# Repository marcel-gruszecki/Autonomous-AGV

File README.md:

# Autonomous AGV Fleet — ESP32 Line Followers in a Scale Warehouse

A fleet of two autonomous guided vehicles (AGVs) that serve a self-built scale
warehouse. Each vehicle runs on a custom ESP32 PCB and follows a taped line network.
A Python control server plans collision-free routes for both robots, and a warehouse
layer on top of it turns deliveries and customer orders into transport jobs.

The project covers the full development cycle: electrical schematic and PCB, hardware
assembly, embedded firmware, multi-robot path planning, and warehouse logistics.

The mechanical platform comes from the *OSOYOO 2WD Robot Car Starter Kit for Arduino*,
which was used as a chassis and drivetrain base only. The stock Arduino Uno and its
motor shield were removed and replaced with a self-designed ESP32-WROOM carrier board,
adding Wi-Fi connectivity and a 32-bit MCU in place of the original 8-bit controller.

## Demo
https://github.com/user-attachments/assets/aa6393ad-4d51-4d18-ae9f-6a0b75ac840b

## Hardware

**Custom PCB (KiCad, manufactured by PCBWay)** — a single-board carrier designed from
scratch, integrating:

- Power section based on LM2596 step-down converters (7.4 V Li-ion pack → 5 V / 3.3 V rails)
- Separate power distribution path for the motor driver
- Connectors for a three-channel TCRT5000 optical line-sensor array
- ESP32-WROOM main circuit with an optimised keepout zone under the RF antenna

**Drivetrain and sensing** — 2× DC gear motors driven through a Model-X dual H-bridge
(PWM speed control on ENA/ENB), 3× TCRT5000 reflective sensors for line detection.

*Electrical schematic: battery and power conversion, ESP32-WROOM module, motor
driver interface, and the line-sensor array (KiCad).*

The board was assembled by hand (T12 soldering station), including component selection,
mechanical integration, and debugging of short-circuit and polarity faults on the first
revision. Both robots use the same PCB revision.

## Warehouse layout

*Scale 1:1, board 200 × 100 cm. CAD source: `Warehouse_model/`.*

The track is a graph of 16 nodes, laid out with 3 cm wide tape. Coordinates are in cm,
(0, 0) is the top-left corner, x grows to the right and y downwards.

| Node | Role | Position |
|------|------|----------|
| `IN1`, `IN2` | Inbound stations — goods arrive here (green) | left edge, y = 38 / 62 |
| `OUT1`, `OUT2` | Outbound stations — goods leave here (red) | right edge, y = 38 / 62 |
| `C1`, `C2`, `C3` | Chargers / robot home positions (blue) | top edge, x = 60 / 100 / 140 |
| `R1`, `R2`, `R3` | Racks, one item type each: `A`→`R1`, `B`→`R2`, `C`→`R3` (yellow) | bottom edge, x = 60 / 100 / 140 |
| `T60` … `T140`, `B60` … `B140` | Intersections of the two horizontal lines with the three vertical lines | y = 38 / 62 |

Stations, chargers and racks are *fields* — dead ends of a line with a stop bar.
A robot drives onto a field, stops on the bar, and turns 180° to leave. The two ends
of each short vertical connector (e.g. `T60`–`B60`) are treated as one place, so only
one robot can be on them at a time.

## Software architecture

```
 warehouse.py  ──HTTP /goal, /status──▶  serwer.py  ◀──HTTP /command, /done──  ESP32 robot 1
 (stock, orders,                         (CBS path planning,                    ESP32 robot 2
  task dispatch)                          command scheduling)
```

- `OSOYOO/` — ESP32 firmware, C++ on the Arduino framework (PlatformIO). PD line
  following on three sensors, turns at intersections, 180° turns on fields.
- `Server/serwer.py` — control server (Flask). Plans paths for all robots together
  and hands each robot one command at a time.
- `Server/mapf.py` — multi-agent path finding: Conflict-Based Search
  with space-time A*, turned into an Action Dependency Graph
  so the robots stay collision-free even though they do not
  move in lock-step.
- `Server/warehouse.py` — warehouse layer: keeps the rack stock, queues deliveries
  and orders, and decides which robot goes where.
- `Scheme/` — KiCad schematic, PCB layout, and Gerber files.
- `Warehouse_model/` — CAD drawing of the warehouse board.

### Robot ↔ server protocol

The robot polls `GET /command?robot=<id>` every 100 ms and receives plain text
`"<id> <COMMAND>"` (`"0 STOP"` = nothing to do). After executing it, the robot confirms
with `GET /done?robot=<id>&id=<id>`. Until the confirmation arrives, the server keeps
returning the same command; the robot recognises the id it has already executed, so a
lost confirmation never makes it drive twice.

| Command | Meaning |
|---------|---------|
| `FORWARD [n]` | Follow the line and stop on the stop bar of a field |
| `FORWARD_AFTER_LINE [n]` | Follow the line and stop with the axle on an intersection; `n` = number of intersections to pass (straight drives are merged) |
| `TURN_LEFT`, `TURN_RIGHT` | Rotate 90° on an intersection |
| `RETURN_LEFT`, `RETURN_RIGHT` | Rotate 180° on a field, away from the neighbouring field |
| `STOP` | Stand still |

### Server HTTP API

| Endpoint | Used by | Description |
|----------|---------|-------------|
| `GET /command?robot=<id>` | robot | Current command, see above |
| `GET /done?robot=<id>&id=<cmd id>` | robot | Confirms a command, updates the robot position |
| `GET /goal?robot=<id>&to=<node>` | warehouse | Sets a goal node and replans all robots; `400 {"error": ...}` if the node is taken |
| `GET /status` | warehouse | State of all robots, see [JSON formats](#json-formats) |

## Getting started

### Requirements

- PlatformIO (CLI or the VS Code extension)
- Python 3.8+ with `pip install -r Server/requirements.txt` (Flask)
- The PC running the server and both robots on the same Wi-Fi network

### 1. Configure and flash each robot

```bash
cd OSOYOO/include
cp config.example.hpp config.hpp
```

Edit `config.hpp`:

```cpp
const char* const WIFI_SSID  = "your-wifi";
const char* const WIFI_PASS  = "your-password";
const char* const SERVER_URL = "http://192.168.1.10:8080";   // IP of the PC running serwer.py

#define ROBOT_ID "1"   // "1" for the first robot, "3" for the second one
```

The robot ids must match the server: robot `1` starts on charger `C1`, robot `3` on
`C3` (configured in `robots` in `Server/serwer.py`). `config.hpp` holds your Wi-Fi
password and is ignored by git.

Flash the robot (repeat for the second one with a different `ROBOT_ID`):

```bash
cd OSOYOO
pio run -t upload          # upload_port in platformio.ini: /dev/ttyUSB0
pio device monitor         # optional: serial log, 115200 baud
```

### 2. Place the robots

Put robot `1` on `C1` and robot `3` on `C3`, facing the edge of the board (away from
the track). On the first start the server assumes exactly this position. After that
it remembers the positions in `server_state.json`; delete that file whenever you put
the robots back on their chargers by hand.

### 3. Start the warehouse and the server

In two terminals, inside `Server/`:

```bash
python warehouse.py            # warehouse layer, interactive terminal
python serwer.py               # control server on port 8080
```

`warehouse.py` keeps retrying until the server answers, so the start order does not
matter. Once the robots connect to Wi-Fi they start polling for commands.

`warehouse.py` options:

```bash
python warehouse.py --simulate [--seed 42]                       # random deliveries and orders
python warehouse.py --replay logs/session_YYYYMMDD_HHMMSS.json   # repeat a recorded session
python warehouse.py --replay <file> --speed 2                    # ... twice as fast
```

`serwer.py --random` sends the robots to random free fields without the warehouse
(useful for testing the path planning alone).

### 4. Give the warehouse work

```
>>> in A IN2       # item A arrived at IN2 -> a robot stores it on rack R1
>>> out A OUT1     # item A requested at OUT1 -> a robot takes it from R1 to OUT1
>>> status         # racks, waiting goods, waiting orders, robot tasks
>>> quit
```

Task priority: orders first (from the rack if it has stock, otherwise cross-docking
straight from an inbound station if the item is waiting there), then storing waiting
goods on racks that are not full (capacity 5). A robot with nothing to do returns to
its charger.

## JSON formats

All files are written atomically (to a `.tmp` file, then renamed), so a crash never
leaves a half-written file. Thanks to them both programs can be restarted at any time
and continue where they stopped.

### `Server/server_state.json` — written by `serwer.py`

Saved after every change of a robot's state.

```json
{
  "next_id": 1761400000,
  "robots": {
    "1": {
      "position": "C1",
      "heading": "S",
      "goal": "R1",
      "actions": [
        {"cmd": "FORWARD", "to": "R1", "heading": "S", "seq": 4, "deps": [["3", 2]]}
      ],
      "current": {
        "id": 1761399999,
        "cmd": "FORWARD_AFTER_LINE 2",
        "actions": [
          {"cmd": "FORWARD", "to": "T60", "heading": "S", "seq": 2, "deps": []},
          {"cmd": "FORWARD", "to": "B60", "heading": "S", "seq": 3, "deps": []}
        ]
      },
      "done_seq": 1
    },
    "3": { "...": "same structure" }
  }
}
```

| Field | Meaning |
|-------|---------|
| `next_id` | Id of the next command. Starts at the Unix time, so ids keep growing across server restarts and a robot never mistakes a new command for an old one |
| `position`, `heading` | Node the robot is on after its last confirmed command and the direction it faces (`N`, `E`, `S`, `W`; `N` = towards the chargers) |
| `goal` | Node the robot should reach, `null` = stay |
| `actions` | Planned actions not sent to the robot yet |
| `current` | Command sent to the robot and waiting for `/done`, `null` if none. `cmd` is the text the robot receives, `actions` are the planned actions it covers |
| `done_seq` | Sequence number of the robot's last finished action |
| action `cmd` / `to` / `heading` | Planned move (`FORWARD`, `TURN_LEFT`, `TURN_RIGHT`, `RETURN`), the node and heading after it |
| action `seq` | Sequence number of the action within its robot |
| action `deps` | `[robot, seq]` pairs: the action may start only after that robot has finished action `seq` (i.e. has left the node this robot is about to enter) |

### `GET /status` — returned by `serwer.py`, read by `warehouse.py`

```json
{
  "1": {"position": "C1", "heading": "N", "home": "C1", "goal": "R1", "busy": true},
  "3": {"position": "C3", "heading": "N", "home": "C3", "goal": null, "busy": false}
}
```

`home` is the robot's charger. `busy` is `true` while the robot has a command in
progress, planned actions, or has not reached its goal yet.

### `Server/warehouse_state.json` — written by `warehouse.py`

Saved after every event and every pickup or drop.

```json
{
  "racks": {"A": 2, "B": 0, "C": 5},
  "inbound": [{"item": "B", "station": "IN1"}],
  "orders": [{"item": "C", "station": "OUT2"}],
  "tasks": {
    "1": {"kind": "store", "item": "A", "pickup": "IN2", "drop": "R1", "stage": "drop"},
    "3": null
  }
}
```

| Field | Meaning |
|-------|---------|
| `racks` | Pieces on each rack, by item type (`A` → `R1`, `B` → `R2`, `C` → `R3`), max 5 |
| `inbound` | Goods waiting at an inbound station, oldest first |
| `orders` | Requests waiting at an outbound station, oldest first |
| `tasks` | Task of each robot, `null` = idle |
| task `kind` | `store` (IN → rack), `deliver` (rack → OUT) or `crossdock` (IN → OUT directly) |
| task `pickup`, `drop` | Where the robot loads and unloads the item |
| task `stage` | `pickup` = driving to the pickup node, `drop` = carrying the item to the drop node |

### `Server/logs/session_<date>_<time>.json` — written by `warehouse.py`

Every run (except `--replay`) records its events, so the same workload can be repeated
later with `--replay`.

```json
{
  "initial_state": { "...": "warehouse_state.json at the start of the session" },
  "events": [
    {"t": 3.2, "type": "delivery", "item": "A", "station": "IN2"},
    {"t": 11.8, "type": "order", "item": "A", "station": "OUT1"}
  ]
}
```

`t` is the time in seconds since the start of the session, `type` is `delivery`
(goods arrived at an inbound station) or `order` (goods requested at an outbound
station).

## Tech stack

KiCad · PCBWay · ESP32-WROOM · C++ / Arduino · PlatformIO · Python · Flask ·
Conflict-Based Search · Action Dependency Graph · HTTP

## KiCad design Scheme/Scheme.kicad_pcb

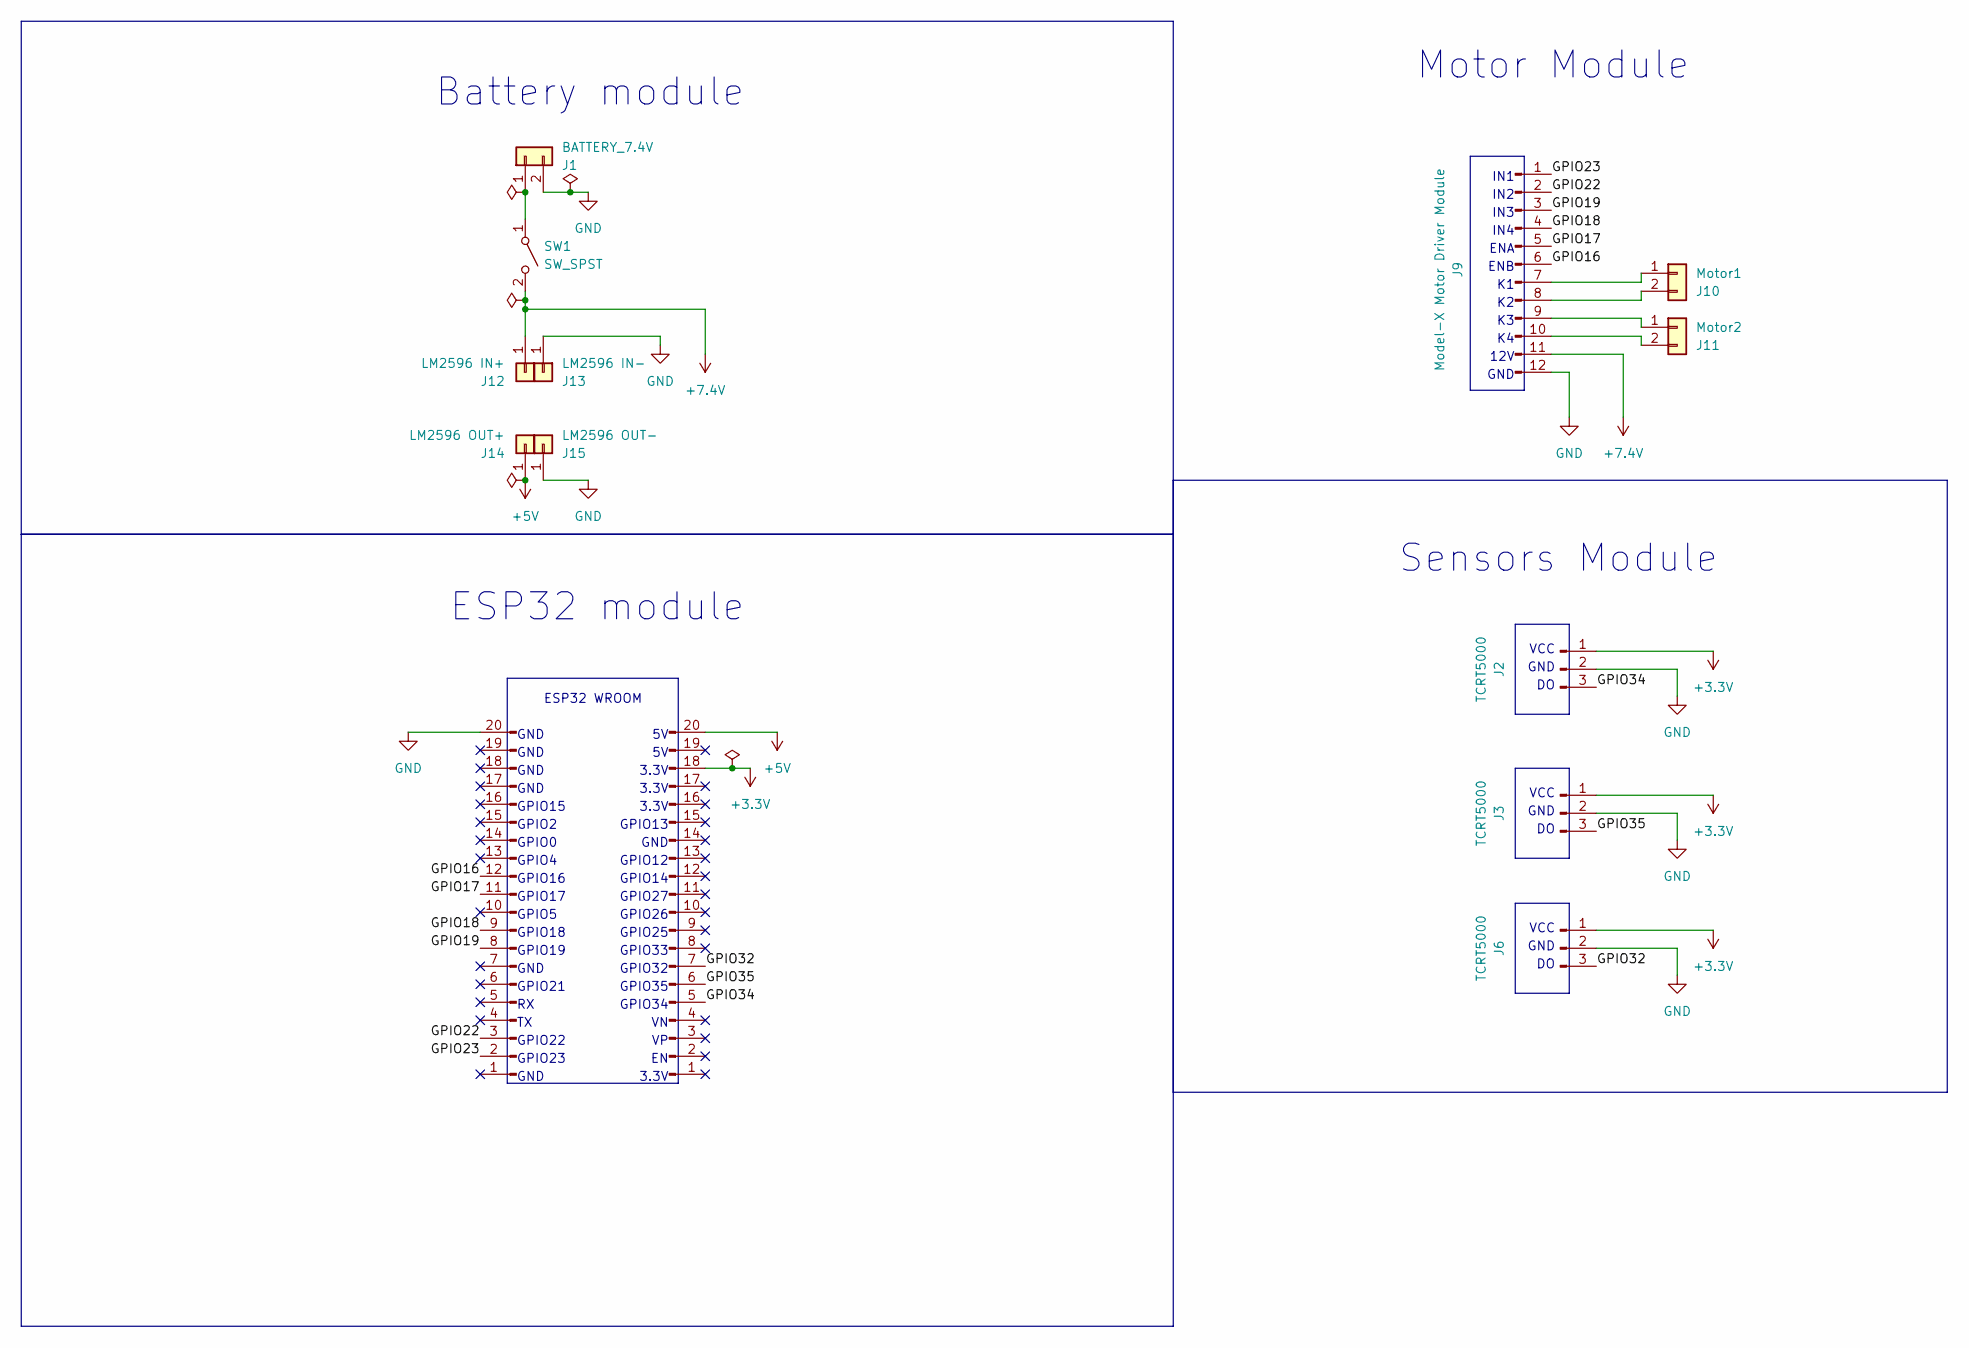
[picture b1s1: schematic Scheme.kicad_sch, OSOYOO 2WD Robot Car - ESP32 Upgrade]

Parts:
J1: BATTERY_7.4V; PinHeader_1x02_P2.54mm_Vertical
J2, J3, J6: TCRT5000; PinSocket_1x03_P2.54mm_Vertical
J4, J5: Conn_01x20_Pin; PinSocket_1x20_P2.54mm_Vertical
J9: Model-X Motor Driver Module; PinSocket_1x12_P2.54mm_Vertical
J10: Motor1; PinHeader_1x02_P2.54mm_Vertical
J11: Motor2; PinHeader_1x02_P2.54mm_Vertical
J12: LM2596 IN+; TestPoint_Pad_3.0x3.0mm
J13: LM2596 IN-; TestPoint_Pad_3.0x3.0mm
J14: LM2596 OUT+; TestPoint_Pad_3.0x3.0mm
J15: LM2596 OUT-; TestPoint_Pad_3.0x3.0mm
SW1: SW_SPST; PinSocket_1x02_P2.54mm_Vertical

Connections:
+3.3V: J2.1, J3.1, J4.18, J6.1
+5V: J4.20, J14.1 (Pin_1_1)
+7.4V: J9.11, J12.1 (Pin_1_1), SW1.2 (B)
/<NO NET>: J4.3
/GPIO16: J5.12, J9.6
/GPIO17: J5.11, J9.5
/GPIO18: J5.9, J9.4
/GPIO19: J5.8, J9.3
/GPIO22: J5.3, J9.2
/GPIO23: J5.2, J9.1
/GPIO32: J4.7, J6.3
/GPIO34: J2.3, J4.5
/GPIO35: J3.3, J4.6
GND: J1.2, J2.2, J3.2, J5.20, J6.2, J9.12, J13.1 (Pin_1_1), J15.1 (Pin_1_1)
unnamed: J1.1, SW1.1 (A)
unnamed: J9.7, J10.1
unnamed: J9.8, J10.2
unnamed: J9.9, J11.1
unnamed: J9.10, J11.2

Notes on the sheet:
12V
GPIO4
GPIO32
ENB
GND
GPIO33
GPIO21
GPIO34
3.3V
GPIO2
GPIO23
Battery module
GPIO18
GPIO22
GPIO12
ESP32 module
IN2
Motor Module
IN1
GPIO14
GPIO17
GPIO27
Sensors Module
IN4
VCC
GPIO19
IN3
GPIO15
GPIO13
GPIO25
GPIO0
GPIO26
ESP32 WROOM
GPIO16
ENA
GPIO35
GPIO5

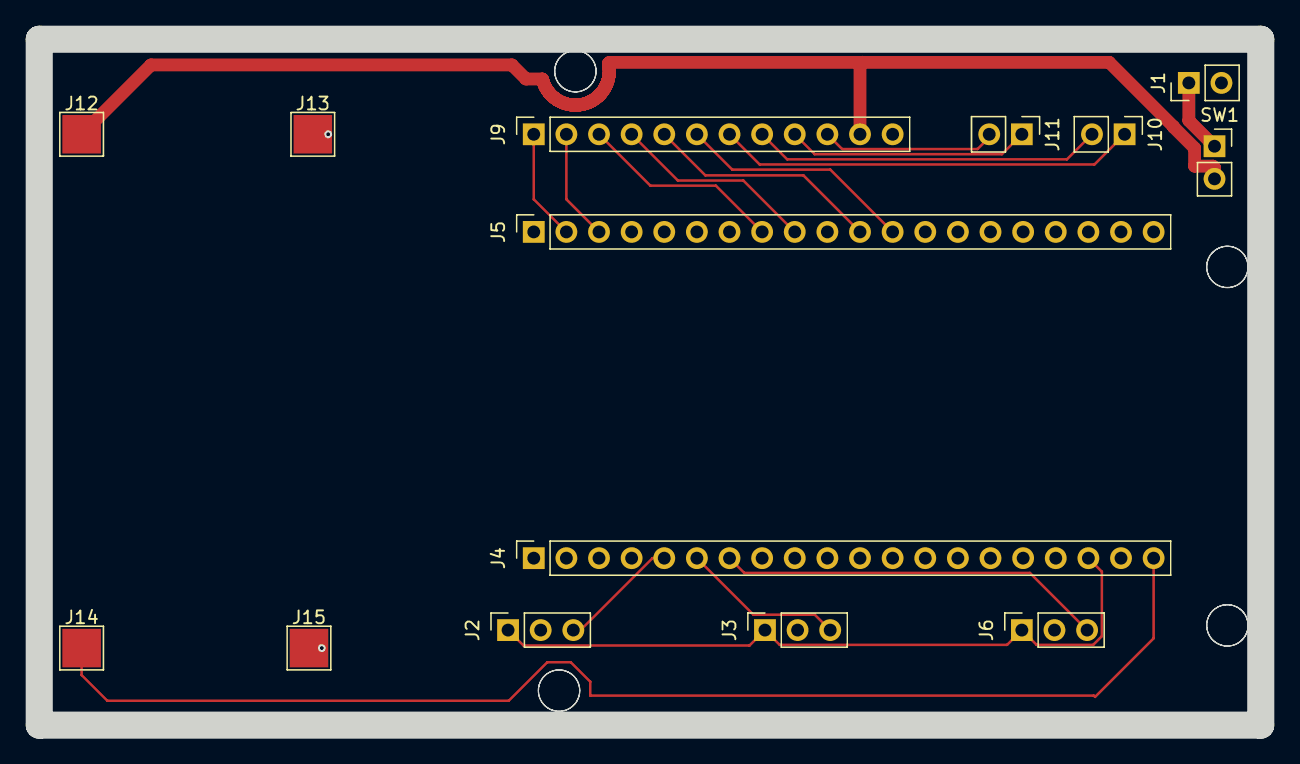
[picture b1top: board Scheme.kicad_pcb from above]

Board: 2 copper layers, 95.1 x 53.4 mm, 14 parts (0 on the bottom side), 18 nets.
